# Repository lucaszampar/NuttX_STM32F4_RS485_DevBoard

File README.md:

# NuttX_STM32F4_RS485_DevBoard

This is the first release of a development board using the STM32F401RCT6 as the main MCU.

### Features Implemented on the Board:
- Digital I2C Temperature Sensor (TMP75)
- 256KB I2C EEPROM
- On-board RS485 Transceiver
- Two Analog Input Stages with Amplifier Buffer
- Two Analog Output Stages with Amplifier Buffer
- MicroSD Connector supporting 1 or 4-bit bus
- Four User LEDs
- Four User Buttons
- USB for DFU (Device Firmware Update) and USB device functionality, as well as powering the board
- Onboard voltage regulator from 5V to 3.3V
- SWD Pins for use as STLink (Pin header) and TC2030-IDC 6-Pin Tag-Connect Plug-of-Nails™ Connector ([More Info](https://www.tag-connect.com/product/tc2030-idc-6-pin-tag-connect-plug-of-nails-spring-pin-cable-with-legs))
- Crystal for HS 8MHz
- Crystal for RTC 32.768KHz
- STL Case available

### 3D Board Render

### Case

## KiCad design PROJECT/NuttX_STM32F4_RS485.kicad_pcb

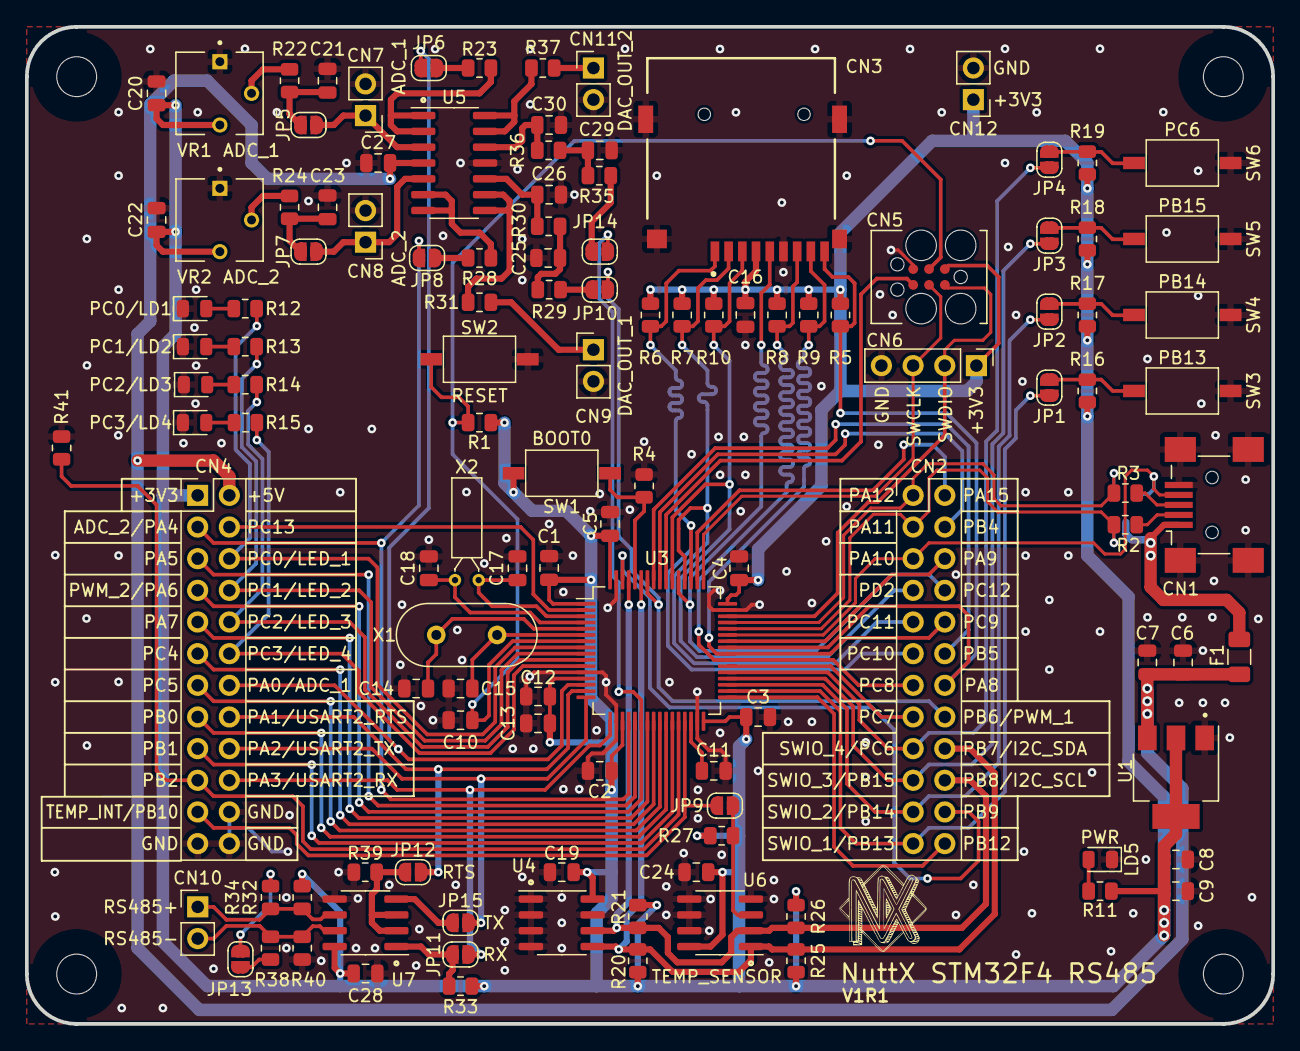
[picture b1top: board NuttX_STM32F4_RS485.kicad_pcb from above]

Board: 2 copper layers, 100.0 x 80.0 mm, 125 parts (1 on the bottom side), 96 nets.

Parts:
C1, C2, C3, C4, C5, C7, C9, C10, C12, C19, C20, C21, C22, C23, C24, C27, C28: 100nF; C_0805_2012Metric
C6, C8, C11, C13, C16: 4u7F; C_0805_2012Metric
C14, C15: 22pF; C_0805_2012Metric
C17, C18: 10pF; C_0805_2012Metric
C25, C26, C29, C30: 10uF; C_0805_2012Metric
CN1: USB_AB_Mini; USB_Mini-AB_10033527-N3112MLF
CN2, CN4: Conn_02x12_Odd_Even; PinHeader_2x12_P2.54mm_Vertical
CN3: Micro_SD_Card; GCT_MEM2075-00-140-01-A
CN5: J-TAG-ADP
CN6: Conn_01x04_Male; PinHeader_1x04_P2.54mm_Vertical
CN7, CN8, CN9, CN10, CN11, CN12: Conn_01x02; PinHeader_1x02_P2.54mm_Vertical
F1: Fuse; Fuse_1206_3216Metric
H1, H2, H3, H4: MountingHole; MountingHole_3.2mm_M3
JP1, JP2, JP3, JP4, JP5, JP6, JP7, JP8, JP9, JP10, JP11, JP12, JP13, JP14, JP15: SolderJumper_2_Open; SolderJumper-2_P1.3mm_Open_RoundedPad1.0x1.5mm
LD1, LD2, LD3, LD4: BLUE; LED_0805_2012Metric
LD5: PWR; LED_0805_2012Metric
R1, R4, R5, R6, R7, R8, R9, R10, R16, R17, R18, R19, R20, R21, R22, R24, R25, R26, R27, R29, R30, R32, R33, R35, R36, R39, R40, R41: 10K; R_0805_2012Metric
R2, R3: 10R; R_0805_2012Metric
R11, R12, R13, R14, R15, R23, R28, R31, R34, R37, R38: 100R; R_0805_2012Metric
SW1: BOOT0; TSB008A2518A
SW2: RESET; TSB008A2518A
SW3: SWIO_1; TSB008A2518A
SW4: SWIO_2; TSB008A2518A
SW5: SWIO_3; TSB008A2518A
SW6: SWIO_4; TSB008A2518A
U1: LM1117-3.3; SOT-223
U2: USBLC6-4SC6Y; SOT-23-6
U3: STM32F401RCT6; LQFP-64_10x10mm_P0.5mm
U4: HX24LC02BDRG; SOIC-8_3.9x4.9mm_P1.27mm
U5: COS724SR; SOIC-14_3.9x8.7mm_P1.27mm
U6: TMP75AIDR; SOIC-8_3.9x4.9mm_P1.27mm
U7: BL3085B; SOIC-8_3.9x4.9mm_P1.27mm
VR1, VR2: 10K; TRIM_3362P-1-502
X1: 8MHZ; Crystal_HC49-U_Vertical
X2: 32.768K; Crystal_DS26_D2.0mm_L6.0mm_Horizontal

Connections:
+3.3V: C1.1, C2.1, C3.1, C4.1, C5.1, C8.1, C9.1, C12.1, C13.1, C16.1, C19.1, C20.1, C22.1, C24.1, C28.1, CN3.4 (VDD), CN4.1, CN5.1 (VTREF), CN6.1, CN12.1, R1.1, R5.1, R6.1, R7.1, R8.1, R9.1, R10.1, R11.1, R16.1, R17.1, R18.1, R19.1, R20.1, R21.1, R25.1, R26.1, R27.1, R32.1, R33.1, SW1.2, U1.2 (VO), U3.1 (VBAT), U3.13 (VREF+), U3.19 (VDD), U3.32 (VDD), U3.48 (VDD), U3.64 (VDD), U4.8 (VCC), U6.8 (+Vs), U7.8 (VCC), VR1.3, VR2.3
+5V: C6.1, C7.1, C27.1, CN4.2, F1.2, U1.3 (VI), U5.4 (V+)
/MCU/ADC_1: CN4.14, JP6.2 (B), U3.14 (PA0)
/MCU/ADC_2: CN4.3, JP8.2 (B), U3.20 (PA4)
/MCU/I2C_SCL: CN2.20, R21.2, R26.2, U3.61 (PB8), U4.6 (SCL), U6.2 (SCL)
/MCU/I2C_SDA: CN2.18, R20.2, R25.2, U3.59 (PB7), U4.5 (SDA), U6.1 (SDA)
/MCU/LED_1: CN4.6, R12.1, U3.8 (PC0)
/MCU/LED_2: CN4.8, R13.1, U3.9 (PC1)
/MCU/LED_3: CN4.10, R14.1, U3.10 (PC2)
/MCU/LED_4: CN4.12, R15.1, U3.11 (PC3)
/MCU/OSC32_IN: C17.1, U3.3 (PC14), X2.1
/MCU/OSC32_OUT: C18.1, U3.4 (PC15), X2.2
/MCU/OSC_IN: C14.1, U3.5 (PH0), X1.1
/MCU/OSC_OUT: C15.1, U3.6 (PH1), X1.2
/MCU/PA5: CN4.5, U3.21 (PA5)
/MCU/PA7: CN4.9, U3.23 (PA7)
/MCU/PA9: CN2.6, U3.42 (PA9)
/MCU/PA15: CN2.2, U3.50 (PA15)
/MCU/PB0: CN4.15, U3.26 (PB0)
/MCU/PB1: CN4.17, U3.27 (PB1)
/MCU/PB2: CN4.19, R41.1, U3.28 (PB2)
/MCU/PB4: CN2.4, U3.56 (PB4)
/MCU/PB5: CN2.12, U3.57 (PB5)
/MCU/PB9: CN2.22, U3.62 (PB9)
/MCU/PB12: CN2.24, U3.33 (PB12)
/MCU/PC4: CN4.11, U3.24 (PC4)
/MCU/PC5: CN4.13, U3.25 (PC5)
/MCU/PC7: CN2.15, U3.38 (PC7)
/MCU/PC13: CN4.4, U3.2 (PC13)
/MCU/PWM_1: CN2.16, JP10.1 (A), U3.58 (PB6)
/MCU/PWM_2: CN4.7, JP14.1 (A), U3.22 (PA6)
/MCU/SDIO_CK: CN2.8, CN3.5 (CLK), U3.53 (PC12)
/MCU/SDIO_CMD: CN2.7, CN3.3 (CMD), R10.2, U3.54 (PD2)
/MCU/SDIO_D0: CN2.13, CN3.7 (DAT0), R8.2, U3.39 (PC8)
/MCU/SDIO_D1: CN2.10, CN3.8 (DAT1), R9.2, U3.40 (PC9)
/MCU/SDIO_D2: CN2.11, CN3.1 (DAT2), R6.2, U3.51 (PC10)
/MCU/SDIO_D3: CN2.9, CN3.2 (DAT3/CD), R7.2, U3.52 (PC11)
/MCU/SD_CD: CN2.14, CN3.CD, R5.2, U3.41 (PA8)
/MCU/SWCLK: CN5.4 (SWCLK), CN6.3, U3.49 (PA14)
/MCU/SWDIO: CN5.2 (SWDIO), CN6.2, U3.46 (PA13)
/MCU/SWIO_1: CN2.23, JP1.1 (A), U3.34 (PB13)
/MCU/SWIO_2: CN2.21, JP2.1 (A), U3.35 (PB14)
/MCU/SWIO_3: CN2.19, JP3.1 (A), U3.36 (PB15)
/MCU/SWIO_4: CN2.17, JP4.1 (A), U3.37 (PC6)
/MCU/SWO: CN5.6 (SWO), U3.55 (PB3)
/MCU/TEMP_INT: CN4.21, JP9.2 (B), U3.29 (PB10)
/MCU/USART2_RTS: CN4.16, JP12.1 (A), U3.15 (PA1)
/MCU/USART2_RX: CN4.20, JP11.1 (A), U3.17 (PA3)
/MCU/USART2_TX: CN4.18, JP15.1 (A), U3.16 (PA2)
/MCU/USB_D+: CN2.1, R3.2, U2.1 (I/O1), U3.45 (PA12)
/MCU/USB_D-: CN2.3, R2.2, U2.6 (I/O4), U3.44 (PA11)
/MCU/USB_ID: CN1.4 (ID), CN2.5, U2.3 (I/O2), U3.43 (PA10)
/MCU/nRST: C10.2, CN5.3 (nRESET), R1.2, SW2.2, U3.7 (NRST)
/Periféricos/RS485+: CN10.1, R32.2, R34.1, U7.6 (A)
/Periféricos/RS485-: CN10.2, R38.1, R40.1, U7.7 (B)
GND: C1.2, C2.2, C3.2, C4.2, C5.2, C6.2, C7.2, C8.2, C9.2, C10.1, C11.2, C12.2, C13.2, C14.2, C15.2, C16.2, C17.2, C18.2, C19.2, C20.2, C21.2, C22.2, C23.2, C24.2, C25.2, C26.2, C27.2, C28.2, C29.2, C30.2, CN1.5 (GND), CN1.6 (Shield), CN3.6 (VSS), CN3.10, CN3.11, CN3.12, CN3.13, CN4.22, CN4.23, CN4.24, CN5.5 (GND), CN6.4, CN7.2, CN8.2, CN9.2, CN11.2, CN12.2, LD1.1 (K), LD2.1 (K), LD3.1 (K), LD4.1 (K), LD5.1 (K), R4.2, R39.2, R40.2, R41.2, SW2.1, SW3.1, SW4.1, SW5.1, SW6.1, U1.1 (GND), U2.2 (GND), U3.12 (VSSA), U3.18 (VSS), U3.31 (VSS), U3.47 (VSS), U3.63 (VSS), U4.1 (A0), U4.2 (A1), U4.3 (A2), U4.4 (GND), U4.7 (WP), U5.11 (V-), U6.4 (GND), U6.5 (A2), U6.6 (A1), U6.7 (A0), U7.5 (GND), VR1.1, VR2.1
unnamed: C11.1, U3.30 (VCAP1)
unnamed: C21.1, JP5.1 (A), R22.2
unnamed: C23.1, JP7.1 (A), R24.2
unnamed: C25.1, R29.2, R30.1
unnamed: C26.1, R30.2, U5.10 (+)
unnamed: C29.1, R35.2, R36.1
unnamed: C30.1, R36.2, U5.12 (+)
unnamed: CN1.2 (D-), R2.1
unnamed: CN1.3 (D+), R3.1
unnamed: CN7.1, JP5.2 (B), U5.3 (+)
unnamed: CN8.1, JP7.2 (B), U5.5 (+)
unnamed: CN9.1, R31.2
unnamed: CN11.1, R37.2
unnamed: JP1.2 (B), R16.2, SW3.2
unnamed: JP2.2 (B), R17.2, SW4.2
unnamed: JP3.2 (B), R18.2, SW5.2
unnamed: JP4.2 (B), R19.2, SW6.2
unnamed: JP6.1 (A), R23.2
unnamed: JP8.1 (A), R28.2
unnamed: JP9.1 (A), R27.2, U6.3 (O.S.)
unnamed: JP10.2 (B), R29.1
unnamed: JP11.2 (B), R33.2, U7.1 (RO)
unnamed: JP12.2 (B), R39.1, U7.2 (~RE), U7.3 (DE)
unnamed: JP13.1 (A), R38.2
unnamed: JP13.2 (B), R34.2
unnamed: JP14.2 (B), R35.1
unnamed: JP15.2 (B), U7.4 (DI)
unnamed: LD1.2 (A), R12.2
unnamed: LD2.2 (A), R13.2
unnamed: LD3.2 (A), R14.2
unnamed: LD4.2 (A), R15.2
unnamed: LD5.2 (A), R11.2
unnamed: R4.1, SW1.1, U3.60 (BOOT0)
unnamed: R22.1, VR1.2
unnamed: R23.1, U5.1, U5.2 (-)
unnamed: R24.1, VR2.2
unnamed: R28.1, U5.6 (-), U5.7
unnamed: R31.1, U5.8, U5.9 (-)
unnamed: R37.1, U5.13 (-), U5.14
VBUS: CN1.1 (VBUS), F1.1, U2.5 (VBUS)

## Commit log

2023-10-16 Added Case files
